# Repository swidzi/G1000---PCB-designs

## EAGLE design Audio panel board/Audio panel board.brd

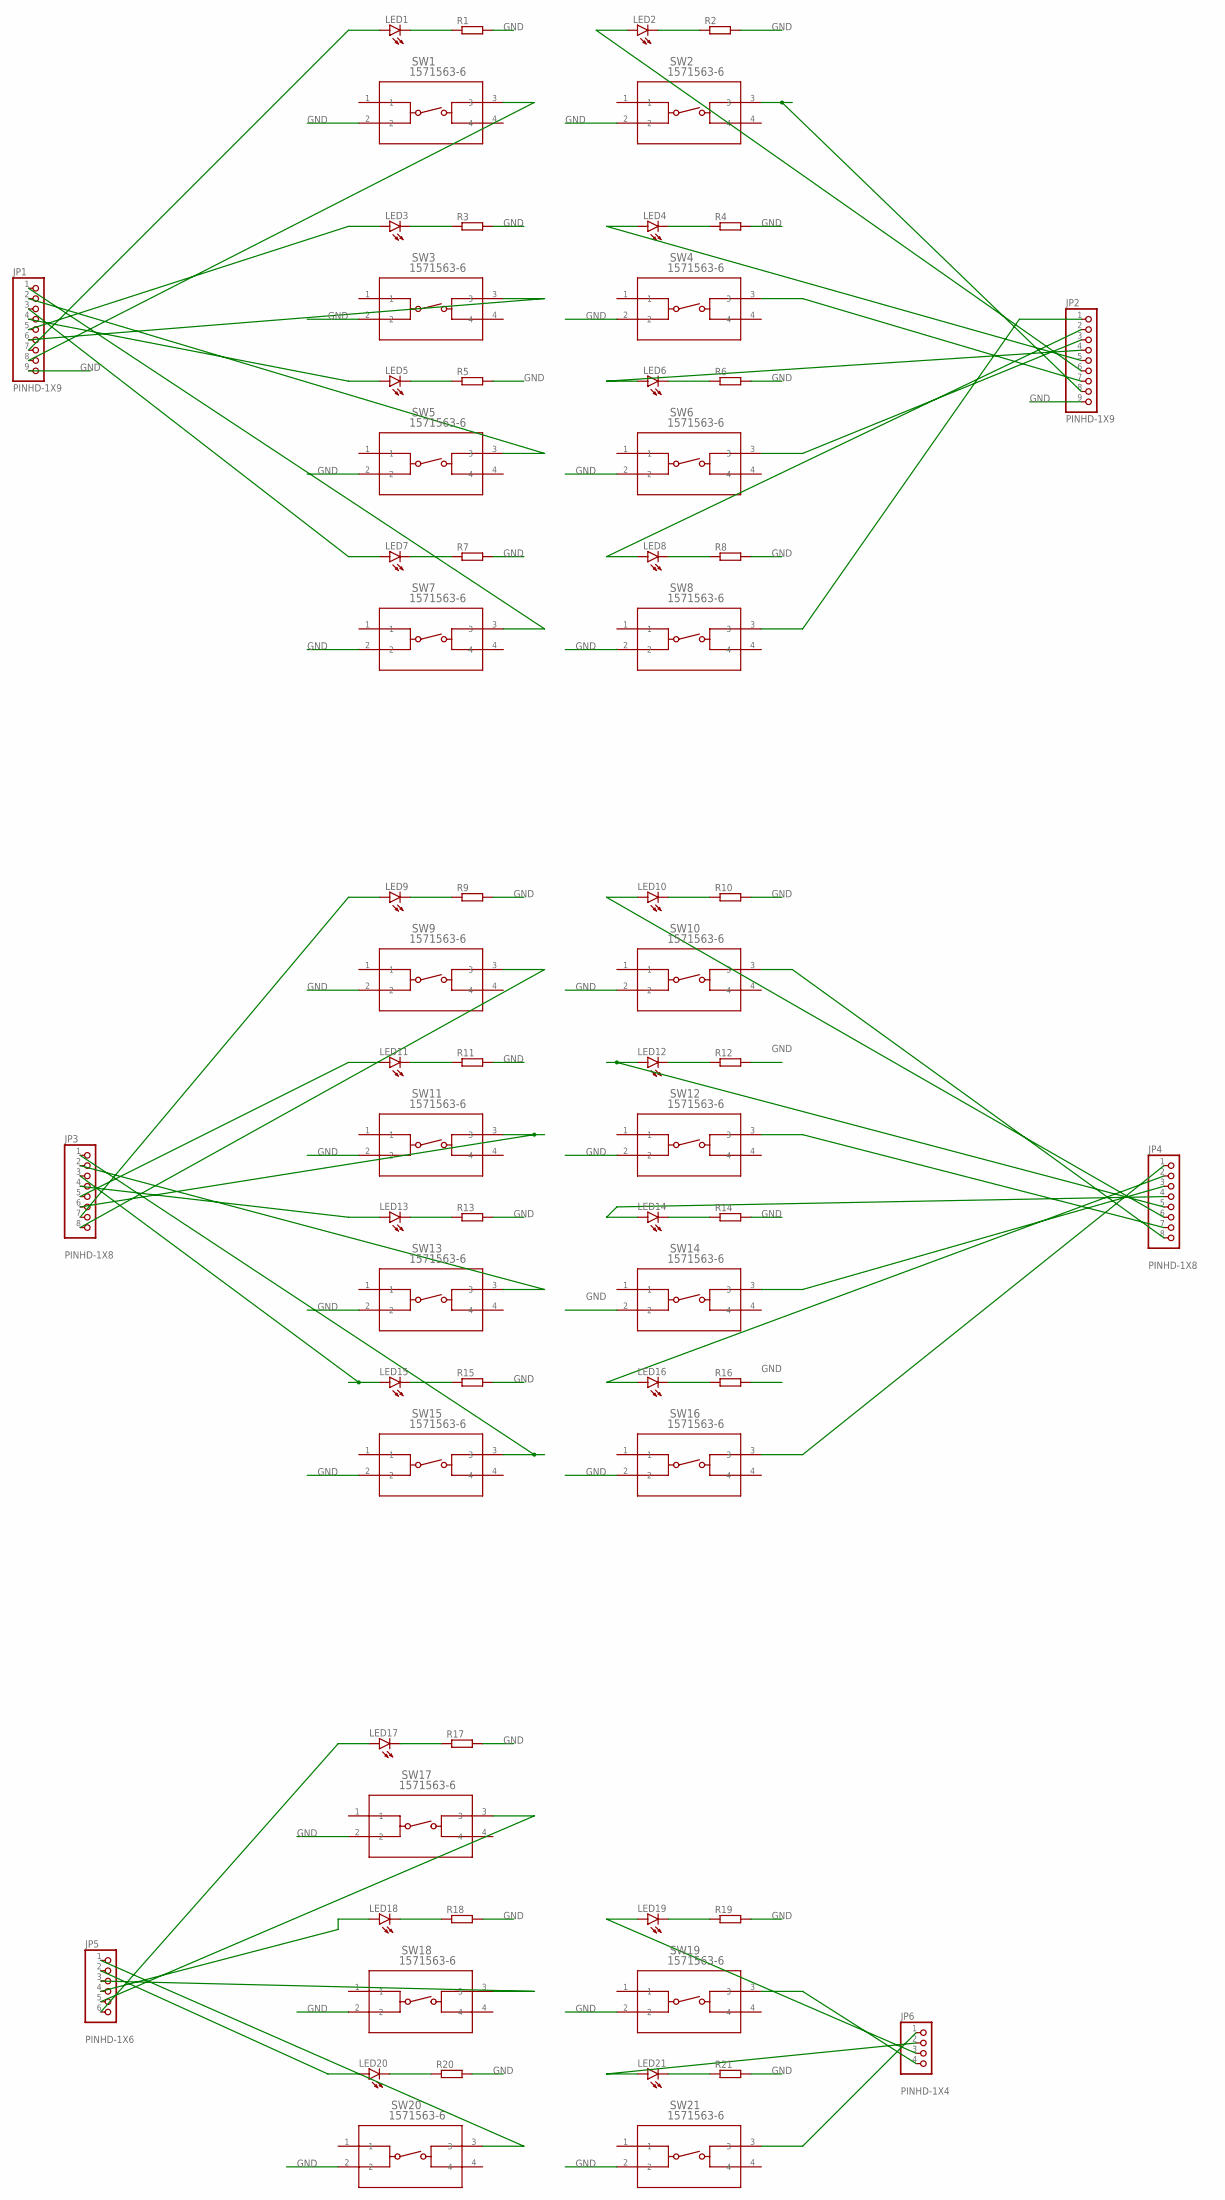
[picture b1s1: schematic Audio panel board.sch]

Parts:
JP1, JP2: PINHD-1X9; 1X09
JP3, JP4: PINHD-1X8; 1X08
JP5: PINHD-1X6; 1X06
JP6: PINHD-1X4; 1X04
LED1, LED2, LED3, LED4, LED5, LED6, LED7, LED8, LED9, LED10, LED11, LED12, LED13, LED14, LED15, LED16, LED17, LED18, LED19, LED20, LED21: LEDCHIP-LED0805; CHIP-LED0805
R1, R2, R3, R4, R5, R6, R7, R8, R9, R10, R11, R12, R13, R14, R15, R16, R17, R18, R19, R20, R21: R-EU_R1206; R1206
SW1, SW2, SW3, SW4, SW5, SW6, SW7, SW8, SW9, SW10, SW11, SW12, SW13, SW14, SW15, SW16, SW17, SW18, SW19, SW20, SW21: 1571563-6; SW4_1437565-E

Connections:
GND: JP1.9, JP2.9, R1.2, R2.2, R3.2, R4.2, R5.2, R6.2, R7.2, R8.2, R9.2, R10.2, R11.2, R12.2, R13.2, R14.2, R15.2, R16.2, R17.2, R18.2, R19.2, R20.2, R21.2, SW1.2, SW2.2, SW3.2, SW4.2, SW5.2, SW6.2, SW7.2, SW8.2, SW9.2, SW10.2, SW11.2, SW12.2, SW13.2, SW14.2, SW15.2, SW16.2, SW17.2, SW18.2, SW19.2, SW20.2, SW21.2
unnamed: JP2.1, SW8.3
unnamed: JP4.8, SW10.3
unnamed: JP5.4, LED18.A
unnamed: LED1.C, R1.1
unnamed: LED2.C, R2.1
unnamed: LED3.C, R3.1
unnamed: JP1.7, LED1.A
unnamed: JP1.5, LED3.A
unnamed: JP2.6, LED2.A
unnamed: JP2.8, SW2.3
unnamed: JP1.8, SW1.3
unnamed: JP1.6, SW3.3
unnamed: LED4.C, R4.1
unnamed: JP2.5, LED4.A
unnamed: JP2.7, SW4.3
unnamed: LED5.C, R5.1
unnamed: JP1.4, LED5.A
unnamed: JP1.2, SW5.3
unnamed: LED6.C, R6.1
unnamed: JP2.4, LED6.A
unnamed: JP2.3, SW6.3
unnamed: LED7.C, R7.1
unnamed: JP1.3, LED7.A
unnamed: JP1.1, SW7.3
unnamed: LED8.C, R8.1
unnamed: JP2.2, LED8.A
unnamed: LED9.C, R9.1
unnamed: JP3.7, LED9.A
unnamed: JP3.8, SW9.3
unnamed: LED10.C, R10.1
unnamed: JP4.6, LED10.A
unnamed: LED11.C, R11.1
unnamed: JP3.5, LED11.A
unnamed: JP3.6, SW11.3
unnamed: LED12.C, R12.1
unnamed: JP4.5, LED12.A
unnamed: JP4.7, SW12.3
unnamed: LED13.C, R13.1
unnamed: JP3.4, LED13.A
unnamed: JP3.2, SW13.3
unnamed: LED14.C, R14.1
unnamed: JP4.4, LED14.A
unnamed: JP4.3, SW14.3
unnamed: LED15.C, R15.1
unnamed: JP3.3, LED15.A
unnamed: JP3.1, SW15.3
unnamed: LED16.C, R16.1
unnamed: JP4.2, LED16.A
unnamed: JP4.1, SW16.3
unnamed: LED17.C, R17.1
unnamed: JP5.6, LED17.A
unnamed: JP5.5, SW17.3
unnamed: LED18.C, R18.1
unnamed: JP5.3, SW18.3
unnamed: LED19.C, R19.1
unnamed: JP6.3, LED19.A
unnamed: JP6.4, SW19.3
unnamed: LED20.C, R20.1
unnamed: JP5.2, LED20.A
unnamed: JP5.1, SW20.3
unnamed: LED21.C, R21.1
unnamed: JP6.2, LED21.A
unnamed: JP6.1, SW21.3

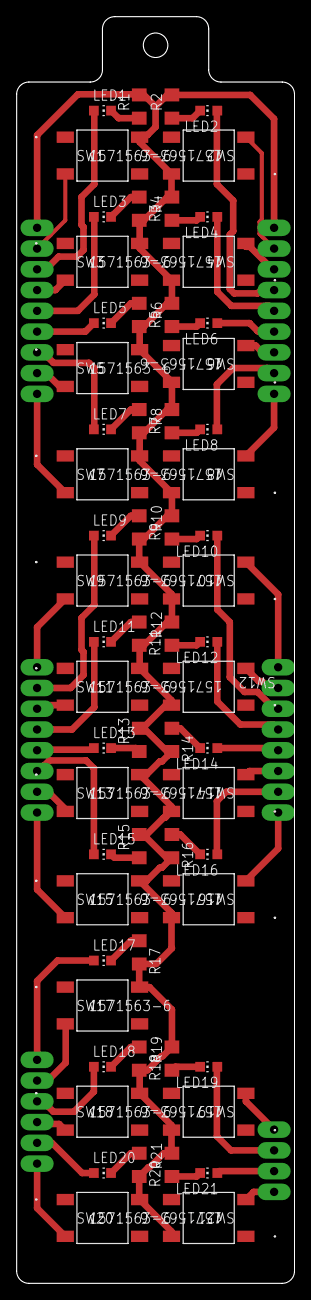
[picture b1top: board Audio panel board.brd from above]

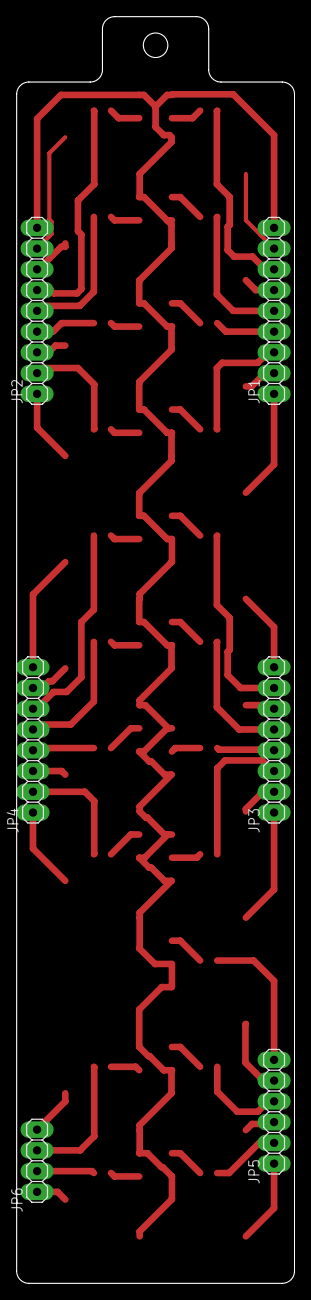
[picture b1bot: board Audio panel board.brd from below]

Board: 2 copper layers, 34.0 x 155.0 mm, 69 parts (6 on the bottom side), 64 nets.

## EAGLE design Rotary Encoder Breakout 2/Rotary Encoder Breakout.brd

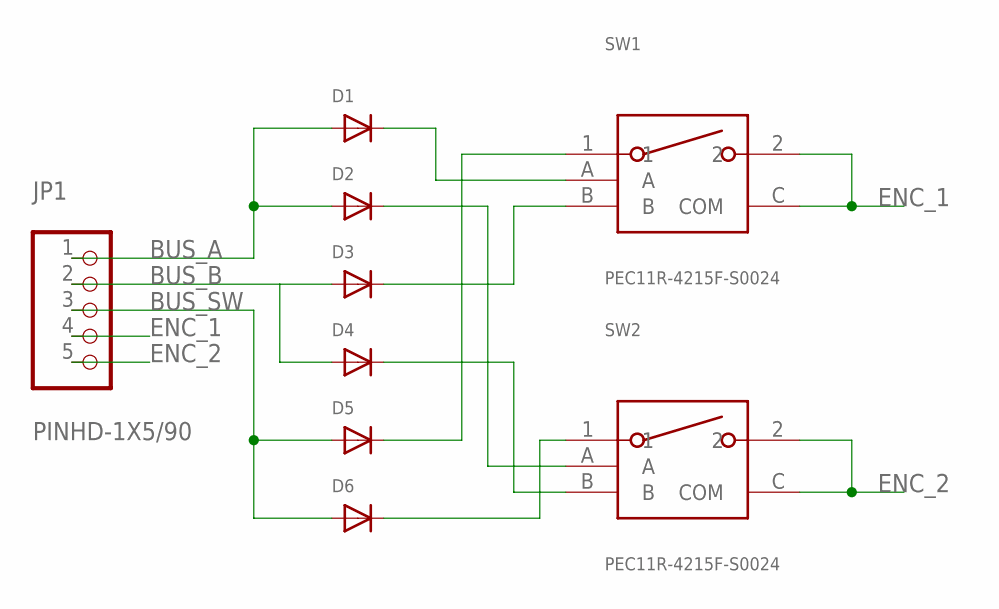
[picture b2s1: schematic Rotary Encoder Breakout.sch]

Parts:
D1, D2, D3, D4, D5, D6: DIODESOD-123; SOD-123
JP1: PINHD-1X5/90; 1X05/90
SW1, SW2: PEC11R-4215F-S0024

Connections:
BUS_A: D1.A, D2.A, JP1.1
BUS_B: D3.A, D4.A, JP1.2
BUS_SW: D5.A, D6.A, JP1.3
ENC_1: JP1.4, SW1.2, SW1.C (COM)
ENC_2: JP1.5, SW2.2, SW2.C (COM)
unnamed: D1.C, SW1.A
unnamed: D2.C, SW2.A
unnamed: D3.C, SW1.B
unnamed: D4.C, SW2.B
unnamed: D5.C, SW1.1
unnamed: D6.C, SW2.1

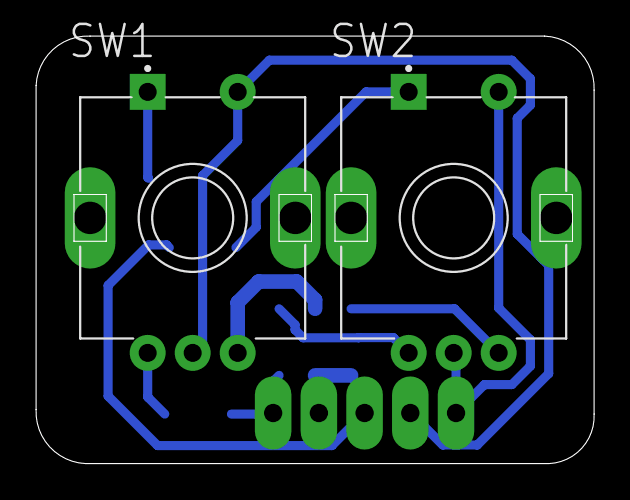
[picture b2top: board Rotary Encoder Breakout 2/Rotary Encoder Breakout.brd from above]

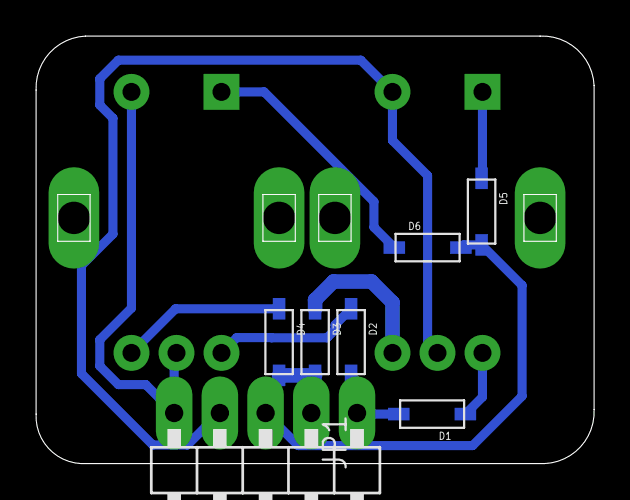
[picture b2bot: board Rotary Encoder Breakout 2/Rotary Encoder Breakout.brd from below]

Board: 2 copper layers, 31.0 x 23.8 mm, 9 parts (7 on the bottom side), 11 nets.

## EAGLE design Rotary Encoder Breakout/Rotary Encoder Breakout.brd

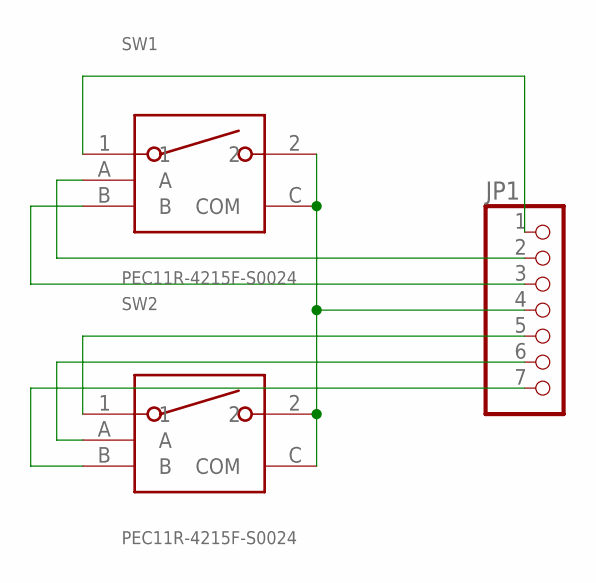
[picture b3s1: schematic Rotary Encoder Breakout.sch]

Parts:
JP1: PINHD-1X07_2.54-90°; 1X07/90
SW1, SW2: PEC11R-4215F-S0024

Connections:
unnamed: JP1.4, SW1.2, SW1.C (COM), SW2.2, SW2.C (COM)
unnamed: JP1.5, SW2.1
unnamed: JP1.6, SW2.A
unnamed: JP1.7, SW2.B
unnamed: JP1.1, SW1.1
unnamed: JP1.2, SW1.A
unnamed: JP1.3, SW1.B

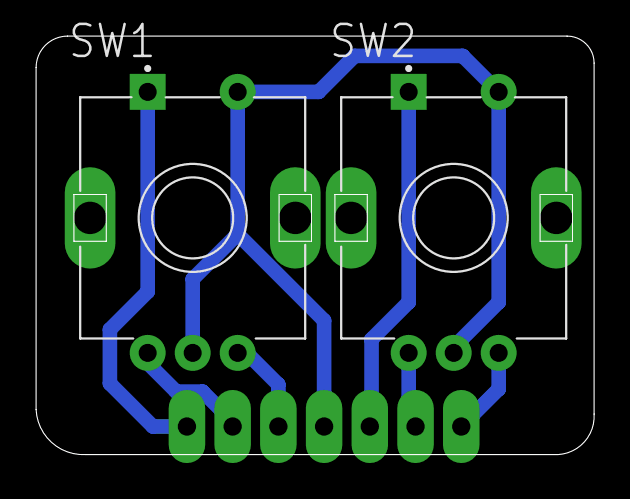
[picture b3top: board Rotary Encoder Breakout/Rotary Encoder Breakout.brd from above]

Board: 2 copper layers, 31.0 x 23.2 mm, 3 parts (1 on the bottom side), 7 nets.

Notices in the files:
parts and their libraries:
COPYRIGHT: Copyright (C) 2016 Accelerated Designs. All rights reserved
